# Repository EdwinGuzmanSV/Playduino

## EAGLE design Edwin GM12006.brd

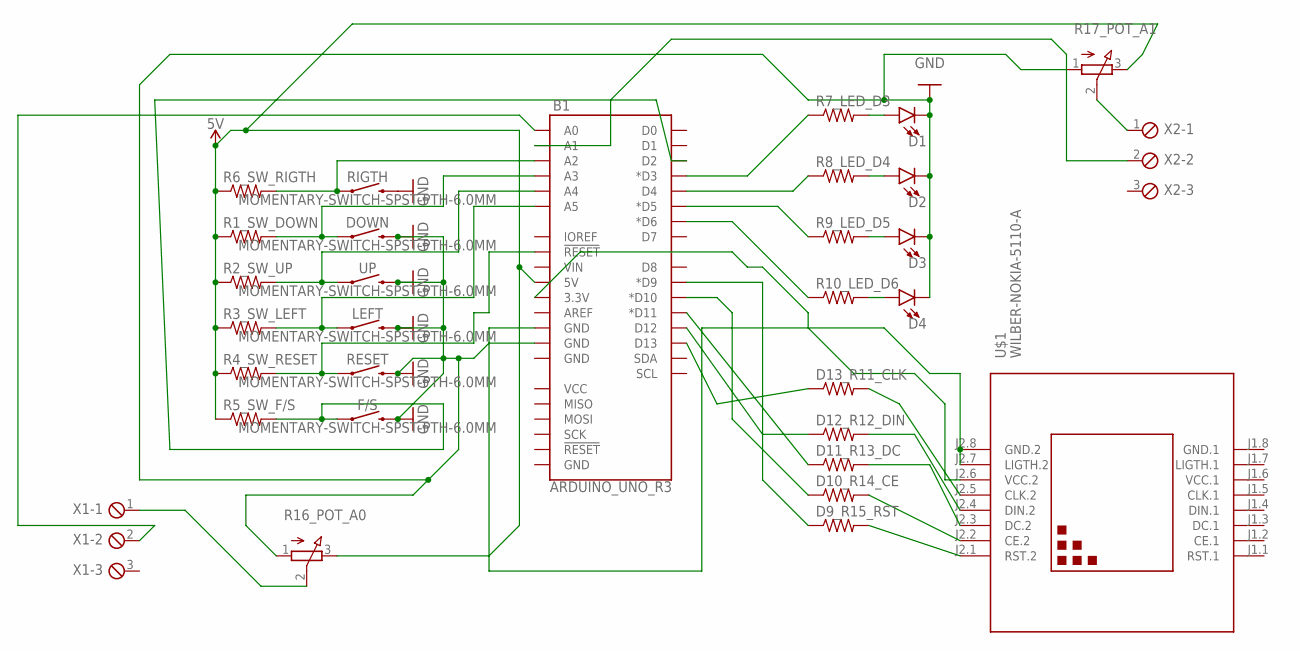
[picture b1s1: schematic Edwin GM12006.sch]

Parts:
B1: ARDUINO_UNO_R3; ARDUINO_R3
D1, D2, D3, D4: LED5MM; LED_5MM
D9_R15_RST, D10_R14_CE, D11_R13_DC, D12_R12_DIN, D13_R11_CLK: R-US_0207/10; 0207/10
DOWN: MOMENTARY-SWITCH-SPST-PTH-6.0MM; TACTILE_SWITCH_PTH_6.0MM
F/S: MOMENTARY-SWITCH-SPST-PTH-6.0MM; TACTILE_SWITCH_PTH_6.0MM
LEFT: MOMENTARY-SWITCH-SPST-PTH-6.0MM; TACTILE_SWITCH_PTH_6.0MM
R1_SW_DOWN, R2_SW_UP, R3_SW_LEFT, R4_SW_RESET, R5_SW_F/S, R6_SW_RIGTH, R7_LED_D3, R8_LED_D4, R9_LED_D5, R10_LED_D6: R-US_0207/10; 0207/10
R16_POT_A0, R17_POT_A1: 3RP/1610N
RESET: MOMENTARY-SWITCH-SPST-PTH-6.0MM; TACTILE_SWITCH_PTH_6.0MM
RIGTH: MOMENTARY-SWITCH-SPST-PTH-6.0MM; TACTILE_SWITCH_PTH_6.0MM
U$1: WILBER-NOKIA-5110-A
UP: MOMENTARY-SWITCH-SPST-PTH-6.0MM; TACTILE_SWITCH_PTH_6.0MM
X1, X2: MPT3; 3POL254

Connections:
5V: B1.5V, R1_SW_DOWN.1, R2_SW_UP.1, R3_SW_LEFT.1, R4_SW_RESET.1, R5_SW_F/S.1, R6_SW_RIGTH.1, R16_POT_A0.3 (E), R17_POT_A1.3 (E)
CE.1: U$1.J1.2 (CE.1)
GND: B1.GND@3 (GND), D1.K (C), D2.K (C), D3.K (C), D4.K (C), DOWN.3 (2), F/S.3 (2), LEFT.3 (2), R16_POT_A0.1 (A), R17_POT_A1.1 (A), RESET.3 (2), RIGTH.3 (2), UP.3 (2)
unnamed: B1.A2, R6_SW_RIGTH.2, RIGTH.1
unnamed: B1.A3, DOWN.1, R1_SW_DOWN.2
unnamed: B1.A4, R2_SW_UP.2, UP.1
unnamed: B1.A5, LEFT.1, R3_SW_LEFT.2
unnamed: B1.RESET@1 (!RESET!), R4_SW_RESET.2, RESET.1
unnamed: B1.D2, F/S.1, R5_SW_F/S.2
unnamed: D1.A, R7_LED_D3.2
unnamed: D2.A, R8_LED_D4.2
unnamed: D3.A, R9_LED_D5.2
unnamed: D4.A, R10_LED_D6.2
unnamed: B1.D3 (*D3), R7_LED_D3.1
unnamed: B1.D4, R8_LED_D4.1
unnamed: B1.D5 (*D5), R9_LED_D5.1
unnamed: B1.D6 (*D6), R10_LED_D6.1
unnamed: D13_R11_CLK.2, U$1.J2.5 (CLK.2)
unnamed: D12_R12_DIN.2, U$1.J2.4 (DIN.2)
unnamed: B1.GND@4 (GND), U$1.J2.7 (LIGTH.2), U$1.J2.8 (GND.2)
unnamed: D11_R13_DC.2, U$1.J2.3 (DC.2)
unnamed: D10_R14_CE.2, U$1.J2.2 (CE.2)
unnamed: D9_R15_RST.2, U$1.J2.1 (RST.2)
unnamed: B1.D13, D13_R11_CLK.1
unnamed: B1.D12, D12_R12_DIN.1
unnamed: B1.D11 (*D11), D11_R13_DC.1
unnamed: B1.D10 (*D10), D10_R14_CE.1
unnamed: B1.D9 (*D9), D9_R15_RST.1
unnamed: B1.3.3V, U$1.J2.6 (VCC.2)
unnamed: R16_POT_A0.2 (S), X1.1
unnamed: B1.A1, X2.2
unnamed: B1.A0, X1.2
unnamed: R17_POT_A1.2 (S), X2.1
RST.1: U$1.J1.1 (RST.1)

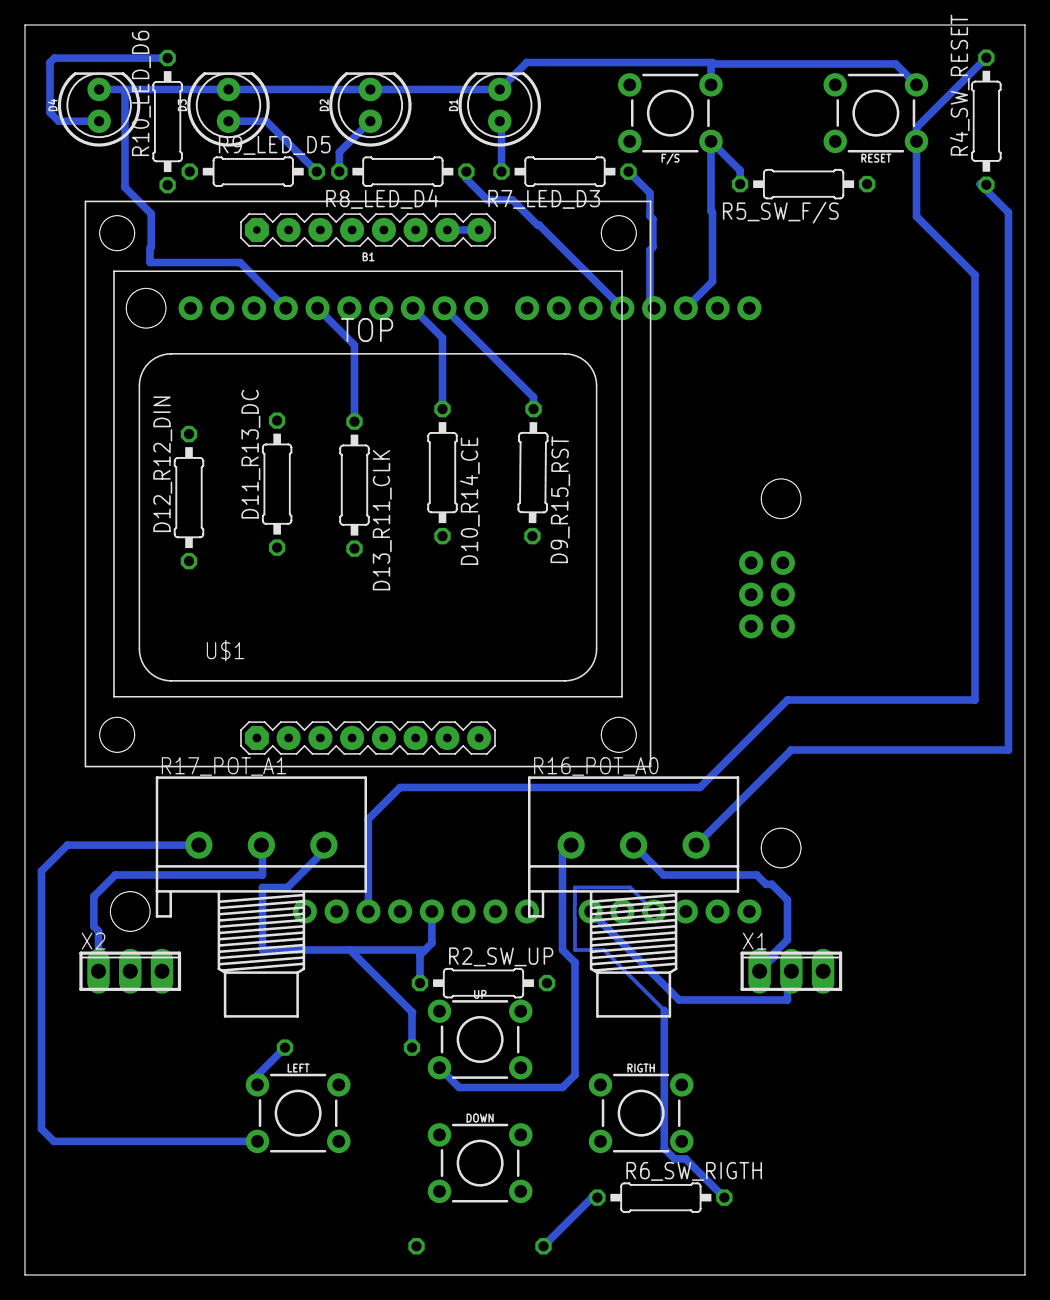
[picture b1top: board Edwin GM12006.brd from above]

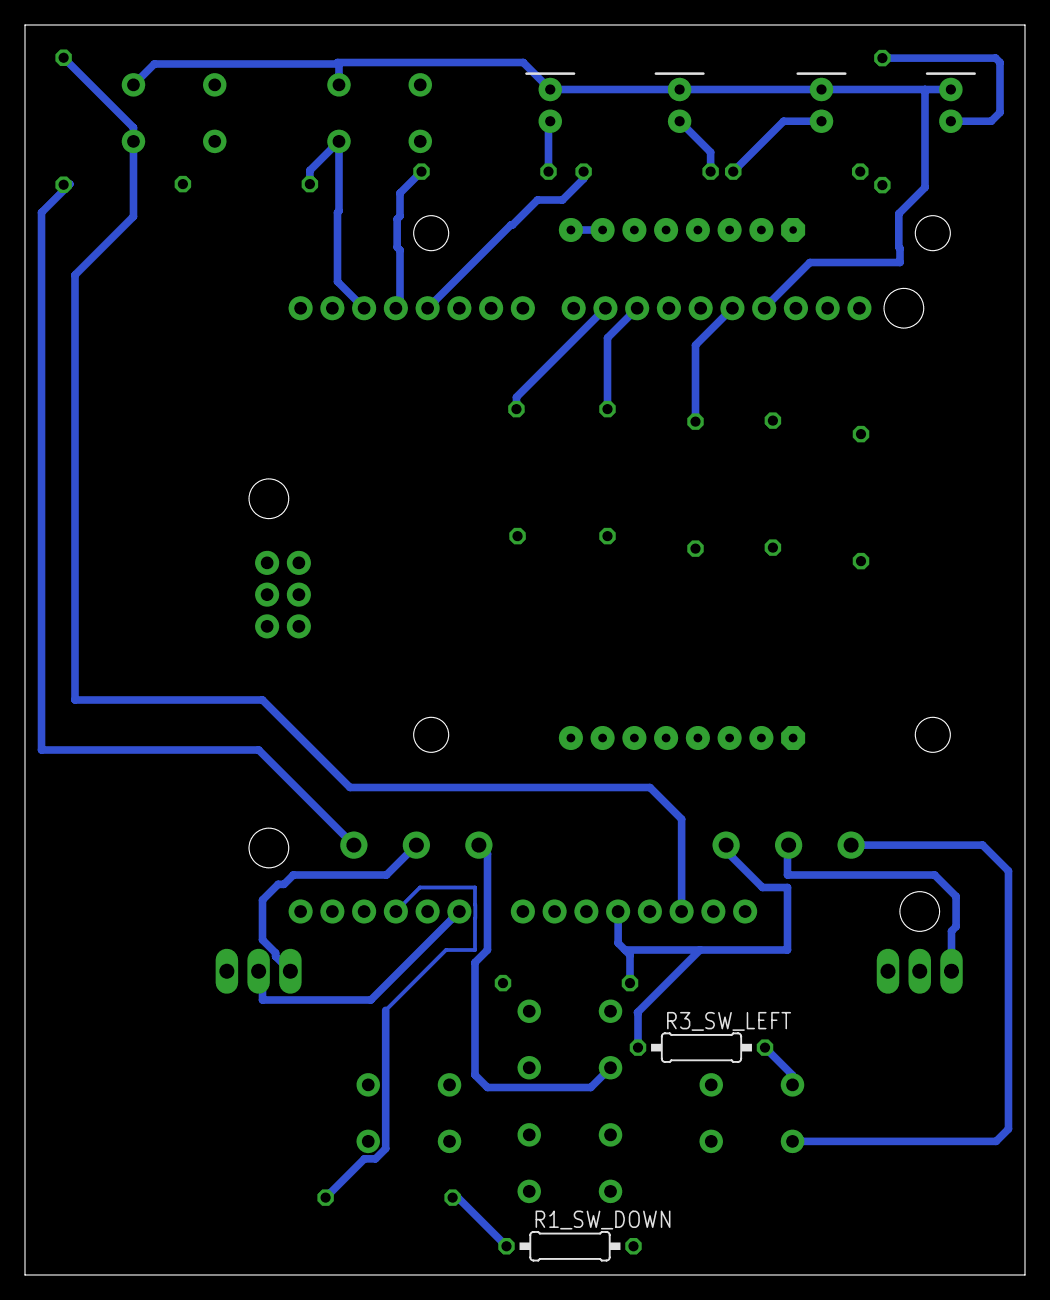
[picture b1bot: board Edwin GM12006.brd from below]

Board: 2 copper layers, 80.0 x 100.0 mm, 31 parts (2 on the bottom side), 32 nets.

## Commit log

2019-03-06 esquematico ha sido finalizado, board siguiendo modelo playduino, demasiadas complicaciones

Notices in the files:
parts and their libraries:
SparkFun-Boards: Licensing: Creative Commons ShareAlike 4.0 International - https://creativecommons.org/licenses/by-sa/4.0
DEA-EBB-Wilber: Released under the Creative Commons Attribution 4.0 International License: http://creativecommons.org/licenses/by/4.0
